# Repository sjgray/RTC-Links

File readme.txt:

RTC Link Devices
================

http://www.cbmsteve.ca/
http://www.cbmsteve.ca/rtclinks/index.html

This is a project to clone and improve the Richmond Telecommunications ("RTC") Devices.

RTC released several different devices including:

* V-Link for VIC-20
* V-Link "64" for C64
* Link for C64
* Link-II for C64
* Mult-Link for C64

I personally own both a Link and Link-II, which I would like to clone. I have started with
the Link-II as it has the most features of the two. Also, the Link-II uses a single PCB
with components on both sides.

Link-II
-------

This is a single PCB with components on both sides. It was done this way to make the PCB
as small as possible so it could fit inside an AMP connector shell. There are two flyouts
that are connected internally into the C64 to make the Link more "transparent" which means
that IO and ROM are invisible when not in use. The Link-II also seems to work without these
connections but might have conflicts with other hardware or software.

First step was to de-solder all the components and scan each side. I then flipped the back-side
scan. Kicad was loaded and a new project created. I then loaded the front side and flipped
back-side as images and then added the components. I added global labels for the busses For the
address and data lines etc. I placed the components in their proper places then traced over the
traces on the images to connect the pins, updating labels where necessary.

Status: I will no be ordering PCB's of this design right away. I am concentrating on the PLUS
        version first as it will be easier to populate

Link-II Plus
------------

Once the Link-II was reverse engineered I decided to make a new version but with all components
on the same side making the board easier to build. I replaced the DIP EPROM with a PLCC version,
and some resistors with a resistor network in order to save space. I also replaced the Link
edge-connector with a pin header to allow a more common IDC ribbon cable.

Status: I ordered some V1.0 PCBs. On testing I discovered an error with resistor R9. This was
        corrected manually on the PCB and the board was tested to work properly.
        The design was updated to V1.1 and boards will be made. This should work correctly.        

Future
------

I would like to clone the original Link design but it uses a double-pcb design. I think the
original design would be ok for most people.

Thank-you
---------

Thanks to Walter Miraglia for helping me test and debug RTC-Link II+ V1.0!

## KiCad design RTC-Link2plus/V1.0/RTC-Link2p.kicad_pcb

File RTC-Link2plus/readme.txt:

RTC-Link II Plus by Steve J. Gray
================

The RTC-Link II was an IEEE Cartridge for the Commodore C64. It enhanced
C64 BASIC by adding the extra disk commands of BASIC V4, plus a full
machine-language monitor. It also adds a "Link" port which enables
multiple computers to access IEEE devices on a sort-of "network".

The original cartridge is a small and simple IEEE interface using a
single PIA chip. To keep the device small it has components on both
sides of the PCB and is able to be mounted inside an AMP connector shell.

This "plus" version is a re-design that retains the same PCB size but with
all components on one side for an easier build. It retains its small size
by using a PLCC EPROM and resistor pack to reduce the component footprints.
Instead of using an edge connector for the "Link" port this version uses
a normal header. There is an option to have two different firmware
revisions, selectable with a jumper.

Pictures/info can be found at: http://www.cbmsteve.ca/rtclinks/
The GitHub repository is here: https://github.com/sjgray/RTC-Links

History
-------

V1.0 - 2023-12-04 Initial design prototype.
V1.1 - 2025-04-04 Fix for R9. To be tested.

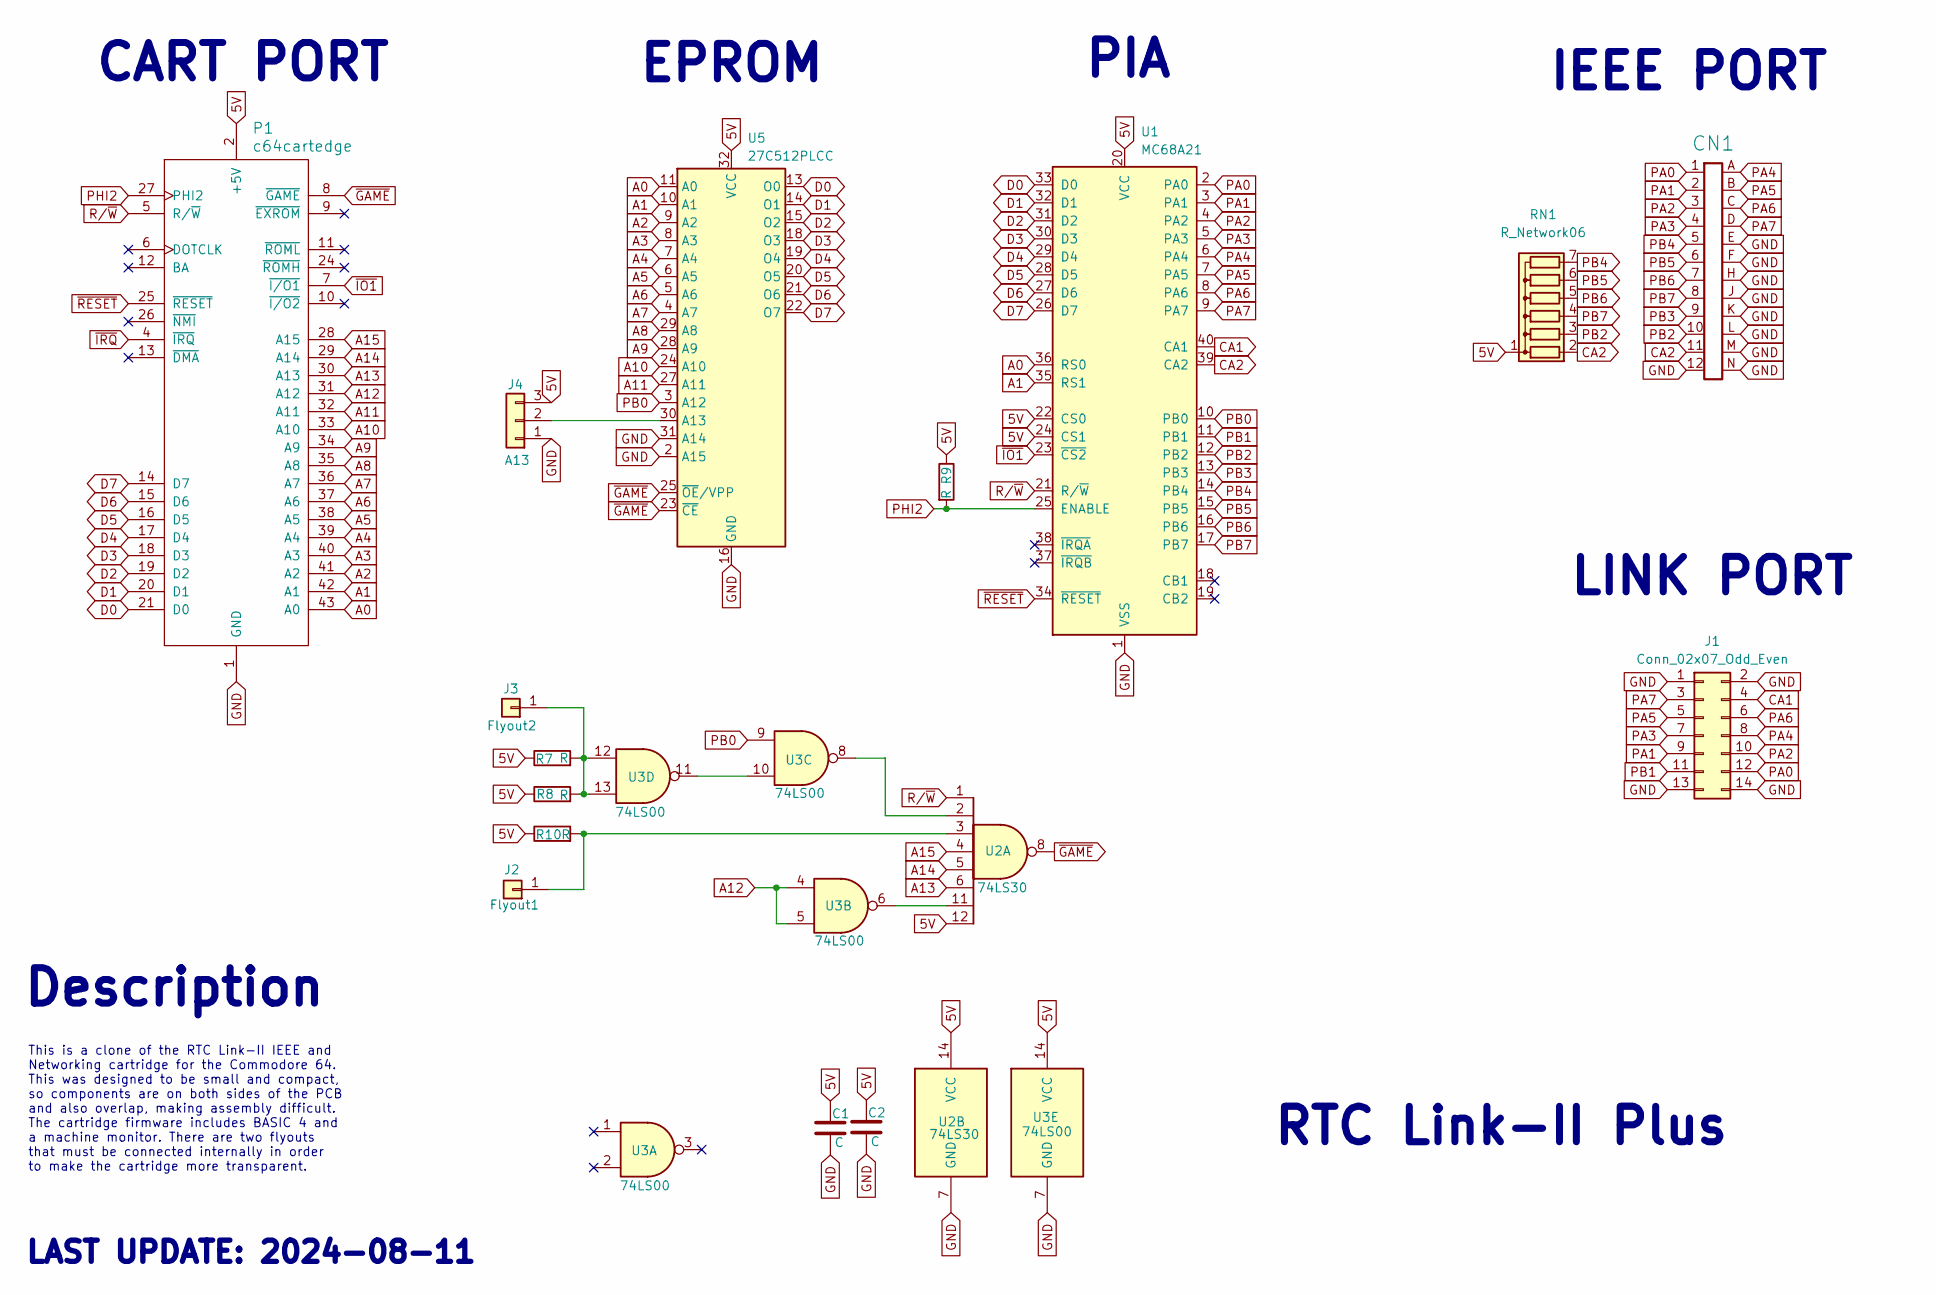
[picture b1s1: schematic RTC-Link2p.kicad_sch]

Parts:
C1, C2: C; C_Disc_D3.0mm_W1.6mm_P2.50mm
CN1: EDGE_CON_02x12; petieee
J1: Conn_02x07_Odd_Even; PinHeader_2x07_P2.54mm_Vertical
J2: Flyout1; PinHeader_1x01_P2.54mm_Vertical
J3: Flyout2; PinHeader_1x01_P2.54mm_Vertical
J4: A13; PinHeader_1x03_P2.54mm_Vertical
P1: c64cartedge
R7, R8, R9, R10: R; R_Axial_DIN0204_L3.6mm_D1.6mm_P7.62mm_Horizontal
RN1: R_Network06; R_Array_SIP7
U1: MC68A21; DIP-40_W15.24mm
U2: 74LS30; DIP-14_W7.62mm_LongPads
U3: 74LS00; DIP-14_W7.62mm_LongPads
U5: 27C512PLCC; PLCC-32_THT-Socket

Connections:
5V: C1.1, C2.1, J4.3, P1.2 (+5V), P1.3 (+5V), R7.1, R8.1, R9.1, R10.1, RN1.1 (common), U1.20 (VCC), U1.22 (CS0), U1.24 (CS1), U2.12, U2.14 (VCC), U3.14 (VCC), U5.32 (VCC)
A0: P1.43 (A0), U1.36 (RS0), U5.11 (A0)
A1: P1.42 (A1), U1.35 (RS1), U5.10 (A1)
A2: P1.41 (A2), U5.9 (A2)
A3: P1.40 (A3), U5.8 (A3)
A4: P1.39 (A4), U5.7 (A4)
A5: P1.38 (A5), U5.6 (A5)
A6: P1.37 (A6), U5.5 (A6)
A7: P1.36 (A7), U5.4 (A7)
A8: P1.35 (A8), U5.29 (A8)
A9: P1.34 (A9), U5.28 (A9)
A10: P1.33 (A10), U5.24 (A10)
A11: P1.32 (A11), U5.27 (A11)
A12: P1.31 (A12), U3.4, U3.5
A13: P1.30 (A13), U2.6
A14: P1.29 (A14), U2.5
A15: P1.28 (A15), U2.4
CA1: J1.4, U1.40 (CA1)
CA2: CN1.11, RN1.2 (R1), U1.39 (CA2)
D0: P1.21 (D0), U1.33 (D0), U5.13 (O0)
D1: P1.20 (D1), U1.32 (D1), U5.14 (O1)
D2: P1.19 (D2), U1.31 (D2), U5.15 (O2)
D3: P1.18 (D3), U1.30 (D3), U5.18 (O3)
D4: P1.17 (D4), U1.29 (D4), U5.19 (O4)
D5: P1.16 (D5), U1.28 (D5), U5.20 (O5)
D6: P1.15 (D6), U1.27 (D6), U5.21 (O6)
D7: P1.14 (D7), U1.26 (D7), U5.22 (O7)
GND: C1.2, C2.2, CN1.12, CN1.E, CN1.F, CN1.H, CN1.J, CN1.K, CN1.L, CN1.M, CN1.N, J1.1, J1.2, J1.13, J1.14, J4.1, P1.1 (GND), P1.22 (GND), P1.23 (GND), P1.44 (GND), U1.1 (VSS), U2.7 (GND), U3.7 (GND), U5.2 (A15), U5.16 (GND), U5.31 (A14)
unnamed: J2.1, R10.2, U2.3
unnamed: J3.1, R7.2, R8.2, U3.12, U3.13
unnamed: J4.2, U5.30 (A13)
unnamed: U2.2, U3.8
unnamed: U2.11, U3.6
unnamed: U3.10, U3.11
PA0: CN1.1, J1.12, U1.2 (PA0)
PA1: CN1.2, J1.9, U1.3 (PA1)
PA2: CN1.3, J1.10, U1.4 (PA2)
PA3: CN1.4, J1.7, U1.5 (PA3)
PA4: CN1.A, J1.8, U1.6 (PA4)
PA5: CN1.B, J1.5, U1.7 (PA5)
PA6: CN1.C, J1.6, U1.8 (PA6)
PA7: CN1.D, J1.3, U1.9 (PA7)
PB0: U1.10 (PB0), U3.9, U5.3 (A12)
PB1: J1.11, U1.11 (PB1)
PB2: CN1.10, RN1.3 (R2), U1.12 (PB2)
PB3: CN1.9, U1.13 (PB3)
PB4: CN1.5, RN1.7 (R6), U1.14 (PB4)
PB5: CN1.6, RN1.6 (R5), U1.15 (PB5)
PB6: CN1.7, RN1.5 (R4), U1.16 (PB6)
PB7: CN1.8, RN1.4 (R3), U1.17 (PB7)
PHI2: P1.27 (PHI2), R9.2, U1.25 (ENABLE)
R/~W: P1.5 (R/~W), U1.21 (R/~W), U2.1
~GAME: P1.8 (~GAME), U2.8, U5.23 (~CE), U5.25 (~OE/VPP)
~IO1: P1.7 (~I/O1), U1.23 (~CS2)
~IRQ: P1.4 (~IRQ)
~RESET: P1.25 (~RESET), U1.34 (~RESET)

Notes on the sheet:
IEEE PORT
Description
EPROM
LAST UPDATE: 2024-08-11
PIA
This is a clone of the RTC Link-II IEEE and Networking cartridge for the Commodore 64. This was designed to be small and compact, so components are on both sides of the PCB and also overlap, making assembly difficult. The cartridge firmware includes BASIC 4 and a machine monitor. There are two flyo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
CART PORT
RTC Link-II Plus
LINK PORT

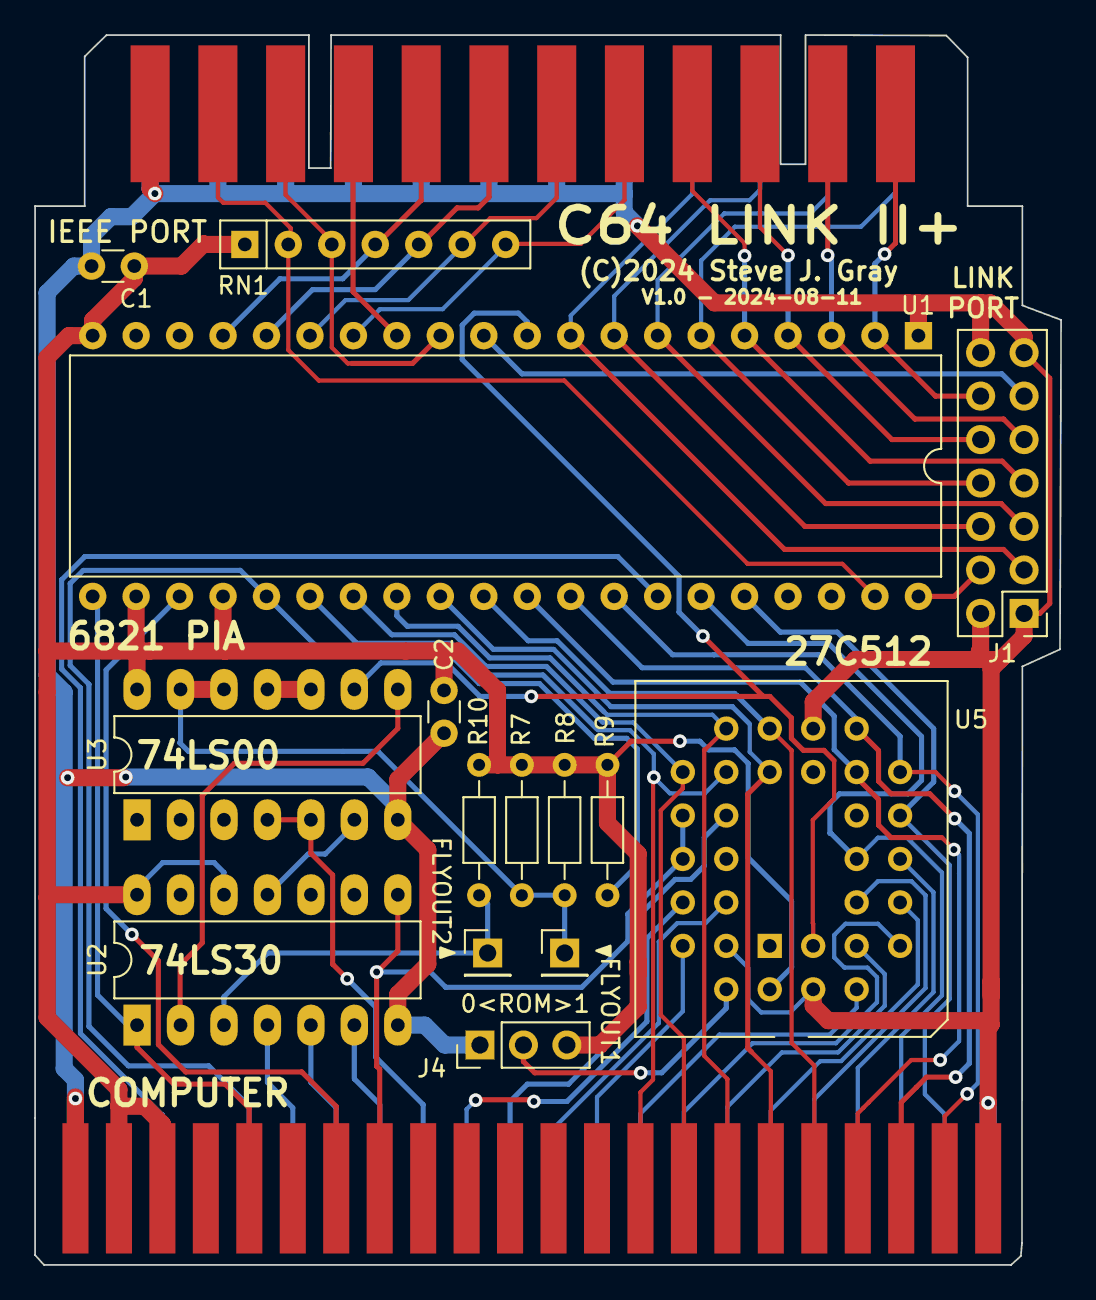
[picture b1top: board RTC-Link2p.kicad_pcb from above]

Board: 2 copper layers, 60.0 x 71.9 mm, 17 parts (0 on the bottom side), 55 nets.

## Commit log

2023-12-18 Initial commit. Link-II and Link-II+
    Completed designs for Link-II and Link-II+. Currently there are no gerbers and the designs have not been verified.
2023-12-18 Add firmware and update readme
    Added firmware and updated readme file.
2025-01-15 Update webpage
    http://www.cbmsteve.ca/
2025-01-19 Fix web link
    http://www.cbmsteve.ca/rtclinks/index.html
2025-03-31 Update to Kicad 9. Add Gerbers, component values, iBom
    Update files to Kicad 9 format. Add Gerbers. Add more component values. Generate interactive BOM. Boards have been made but not tested. Use at own risk!
2025-04-04 Update original to V1.1. R9 fix.
    I populated the V1.0 "plus" version pcb and discovered an error with R9. It was manually corrected on the pcb and the design works correctly. This original board requires the same fix.
    This V1.1 update **should** work but has not been tested as of yet. Use at own risk!
    Added component values on schematic. Updated files to work on Kicad 9. Added readme file.
2025-04-04 Release RTC Link II+ V1.1
    V1.0 was built and there was an error with R9. This is now fixed in V1.1. Each version now has it's own folder. Add readme files, interactive BOM. firmware files.

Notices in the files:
RTC-Link2plus/V1.0/RTC-Link2p.kicad_pcb:
(C)2024 Steve J. Gray
